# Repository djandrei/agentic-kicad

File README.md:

# Agentic KiCad

This fork of [KiCad](https://kicad.org) lets an AI agent design electronics with KiCad's own
engine. An MCP server runs inside KiCad, and every program is available to the agent as
structured tools (148 of them): schematics and hierarchy, symbol and footprint libraries,
boards with interactive routing, length tuning and zones, ERC and DRC, SPICE simulation, 3D,
Gerbers, drawing sheets, the calculator and footprint assignment. Any MCP client works,
for example Claude Code:

```bash
claude mcp add kicad -- /path/to/kicad-cli mcp --stdio      # headless
kicad --mcp-port 0                                          # with viewers; prints the URL and token
```

Every change is saved at once and is one step of the project's file history, so `undo`
and `redo` work across all programs. In viewer mode a person watches read-only viewers that
follow the agent (they never change the design) and can pause it. `kicad --classic` starts
KiCad's usual GUI. Fork code lives in `agentic/`; upstream files are touched only by small,
documented hooks, and the fork is off unless built with `-DKICAD_AGENTIC=ON`.

Documentation: [overview](doc/agentic/README.md), [connecting a client](doc/agentic/clients.md),
[tool reference](doc/agentic/tools.md), [upstream merges](doc/agentic/upstream-merge.md).

### The viewers

The pictures below come from one session in which an agent designed a 4-layer sensor board
and simulated its amplifier stage.

| | |
|---|---|
|  |  |
| **Hub**: open projects, their files, every call the agent makes, a button per viewer and Pause. | **Schematic**: follows the sheet the agent edits and highlights the change; hierarchy, ERC and nets beside it. |
|  |  |
| **PCB**: the board as the agent routes it, with layers, unrouted connections and DRC results. | **3D**: reloads after each board change and uses the camera the agent sets. |
|  |  |
| **Symbol editor**: the symbol the agent builds or inspects, unit by unit, with its pins. | **Footprint editor**: the footprint being built, with its pads. |
|  | |
| **Simulator**: the signals and measurements of the last ngspice run, with the netlist. | |

---

# KiCad README

For specific documentation about [building KiCad](https://dev-docs.kicad.org/en/build/), policies
and guidelines, and source code documentation see the
[Developer Documentation](https://dev-docs.kicad.org) website.

You may also take a look into the [Wiki](https://gitlab.com/kicad/code/kicad/-/wikis/home),
the [contribution guide](https://dev-docs.kicad.org/en/contribute/).

For general information about KiCad and information about contributing to the documentation and
libraries, see our [Website](https://kicad.org/) and our [Forum](https://forum.kicad.info/).

## Build state

KiCad uses a host of CI resources.

GitLab CI pipeline status can be viewed for Linux and Windows builds of the latest commits.

## Release status

## Files
* [AUTHORS.txt](AUTHORS.txt) - The authors, contributors, document writers and translators list
* [CMakeLists.txt](CMakeLists.txt) - Main CMAKE build tool script
* [copyright.h](copyright.h) - A very short copy of the GNU General Public License to be included in new source files
* [Doxyfile](Doxyfile) - Doxygen config file for KiCad
* [INSTALL.txt](INSTALL.txt) - The release (binary) installation instructions
* [uncrustify.cfg](uncrustify.cfg) - Uncrustify config file for uncrustify sources formatting tool
* [_clang-format](_clang-format) - clang config file for clang-format sources formatting tool

## Subdirectories

* [3d-viewer](3d-viewer)         - Sourcecode of the 3D viewer
* [cmake](cmake)      - Modules for the CMAKE build tool
* [common](common)            - Sourcecode of the common library
* [cvpcb](cvpcb)             - Sourcecode of the CvPCB tool
* [demos](demos)             - Some demo examples
* [doxygen](doxygen)     - Configuration for generating pretty doxygen manual of the codebase
* [eeschema](eeschema)          - Sourcecode of the schematic editor
* [gerbview](gerbview)          - Sourcecode of the gerber viewer
* [include](include)           - Interfaces to the common library
* [kicad](kicad)             - Sourcecode of the project manager
* [libs](libs)           - Sourcecode of KiCad utilities (geometry and others)
* [pagelayout_editor](pagelayout_editor) - Sourcecode of the pagelayout editor
* [patches](patches)           - Collection of patches for external dependencies
* [pcbnew](pcbnew)           - Sourcecode of the printed circuit board editor
* [plugins](plugins)           - Sourcecode for the 3D viewer plugins
* [qa](qa)                - Unit testing framework for KiCad
* [resources](resources)         - Packaging resources such as bitmaps and operating system specific files
    - [bitmaps_png](resources/bitmaps_png)       - Menu and program icons
    - [project_template](resources/project_template)          - Project template
* [thirdparty](thirdparty)           - Sourcecode of external libraries used in KiCad but not written by the KiCad team
* [tools](tools)             - Helpers for developing, testing and building
* [translation](translation) - Translation data files (managed through [Weblate](https://hosted.weblate.org/projects/kicad/master-source/) for most languages)
* [utils](utils)             - Small utils for KiCad, e.g. IDF, STEP, and OGL tools and converters

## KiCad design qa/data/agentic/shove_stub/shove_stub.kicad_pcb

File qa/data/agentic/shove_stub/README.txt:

The eco_logger board of the third scripted tool test, before U2.6 -> J2.2 was routed. That route
needs shove mode, and the shove broke the +5V track next to J2.2 into two pieces that led nowhere
(the net stayed connected another way); pcb_route now removes such copper (test_tool_findings.py).

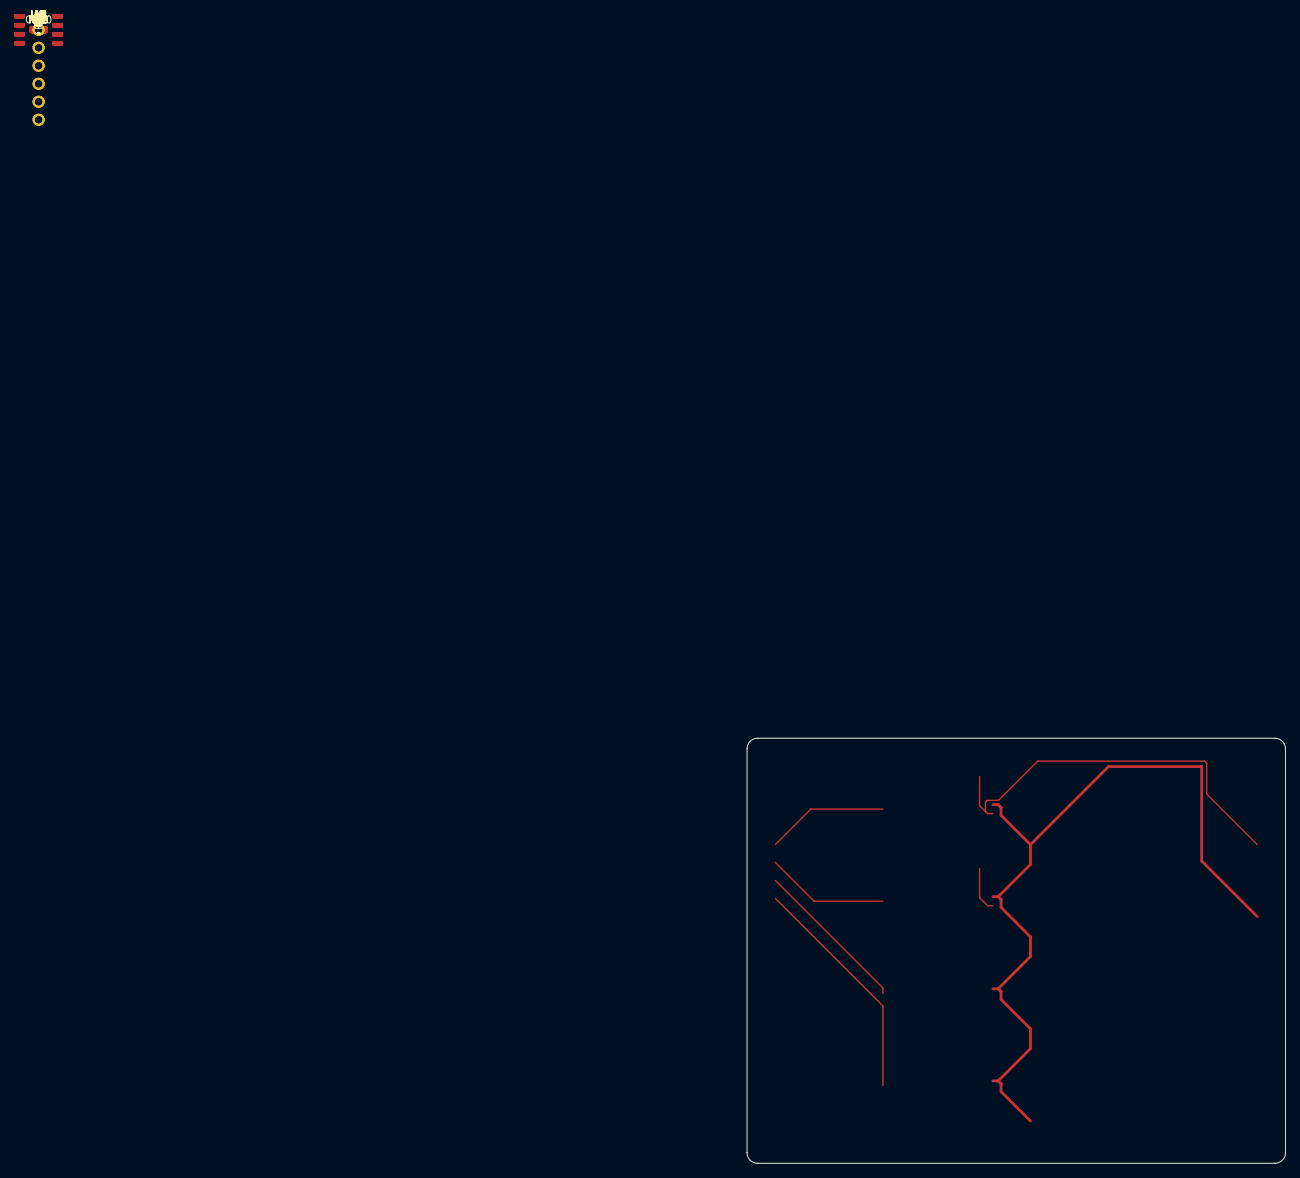
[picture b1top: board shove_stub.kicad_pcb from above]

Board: 2 copper layers, 76.0 x 60.0 mm, 23 parts (0 on the bottom side), 14 nets.

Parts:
C1, C2, C3, C4: 100n; R_0603_1608Metric
C100: 10u; R_0603_1608Metric
J1: INPUTS; HDR6
J2: OUTPUTS; HDR6
R1, R4, R7, R10: 100; R_0603_1608Metric
R2, R5, R8, R11: 1k; R_0603_1608Metric
R3, R6, R9, R12: 10k; R_0603_1608Metric
U1, U2, U3, U4: OPA; SOIC-8

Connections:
+5V: C1.1, C2.1, C3.1, C4.1, C100.1, J2.5, U1.7 (V+), U2.7 (V+), U3.7 (V+), U4.7 (V+)
/IN1: J1.1, R1.1
/IN2: J1.2, R4.1
/IN3: J1.3, R7.1
/IN4: J1.4, R10.1
/OUT1: J2.1, R3.2, U1.6
/OUT2: J2.2, R6.2, U2.6
/OUT3: J2.3, R9.2, U3.6
/OUT4: J2.4, R12.2, U4.6
/ch1/N: R1.2, R2.1, R3.1, U1.2 (-), U1.3 (+)
/ch2/N: R4.2, R5.1, R6.1, U2.2 (-), U2.3 (+)
/ch3/N: R7.2, R8.1, R9.1, U3.2 (-), U3.3 (+)
/ch4/N: R10.2, R11.1, R12.1, U4.2 (-), U4.3 (+)
GND: C1.2, C2.2, C3.2, C4.2, C100.2, J1.5, J1.6, J2.6, R2.2, R5.2, R8.2, R11.2, U1.4 (V-), U2.4 (V-), U3.4 (V-), U4.4 (V-)

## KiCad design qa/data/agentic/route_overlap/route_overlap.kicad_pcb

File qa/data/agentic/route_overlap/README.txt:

The psu_monitor board of the second scripted tool test, without the /ALERT tracks and the zones.
Routing J2.3 -> U1.7 and then U1.7 -> R6.1 here made the second route follow the first one's
track out of U1.7, doubling 4.5 mm of copper (test_tool_findings.py).

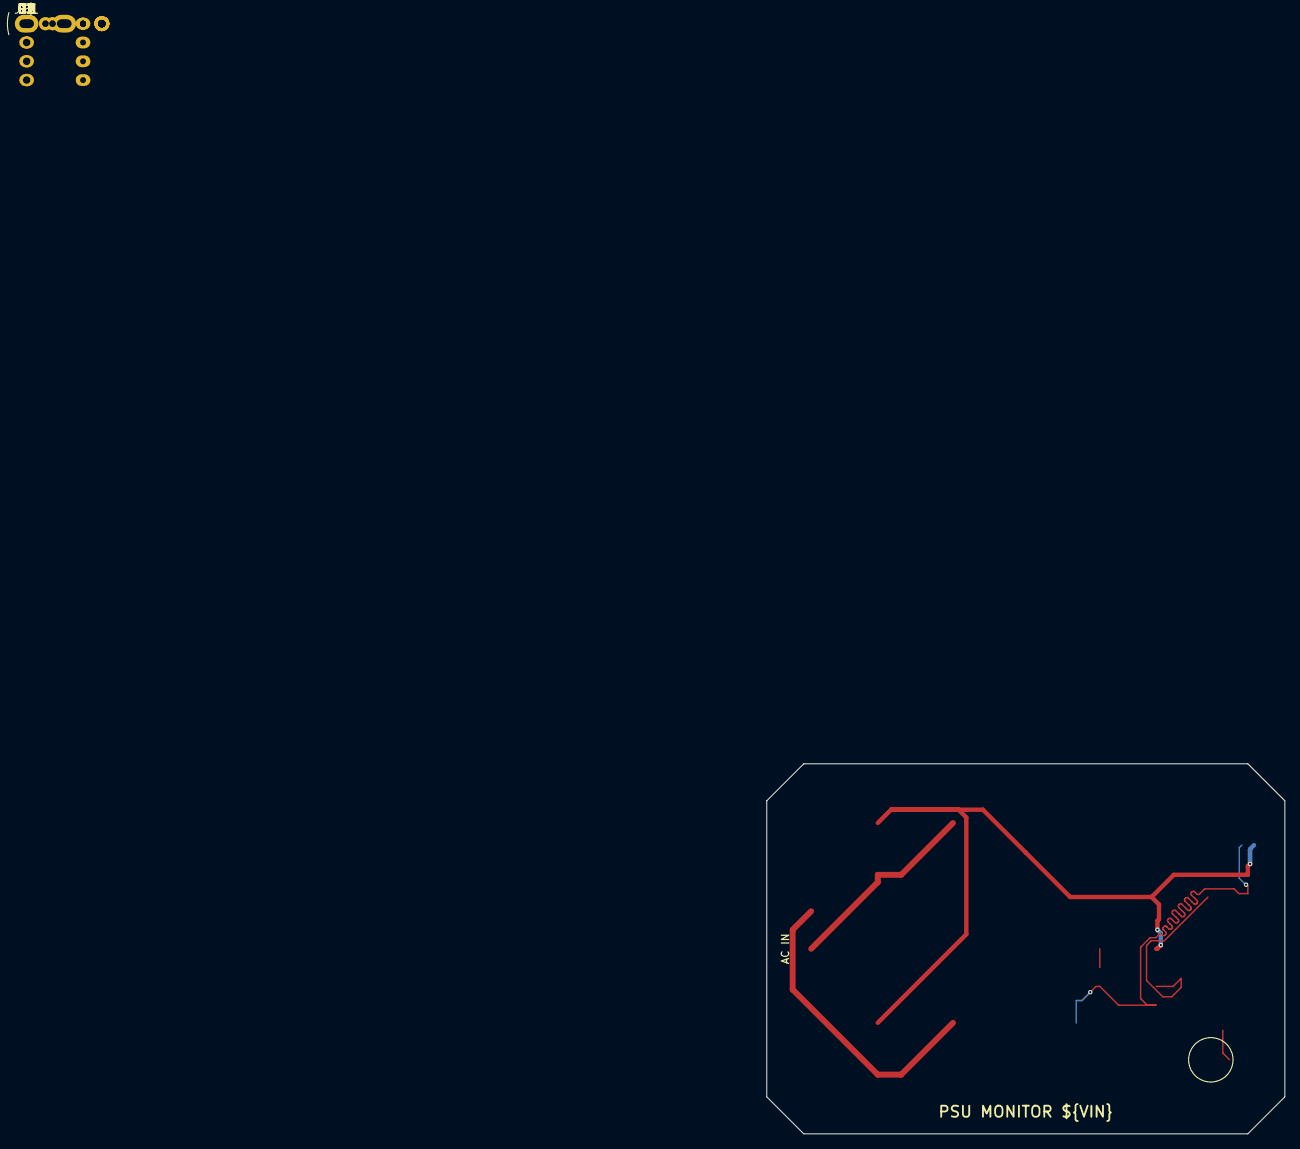
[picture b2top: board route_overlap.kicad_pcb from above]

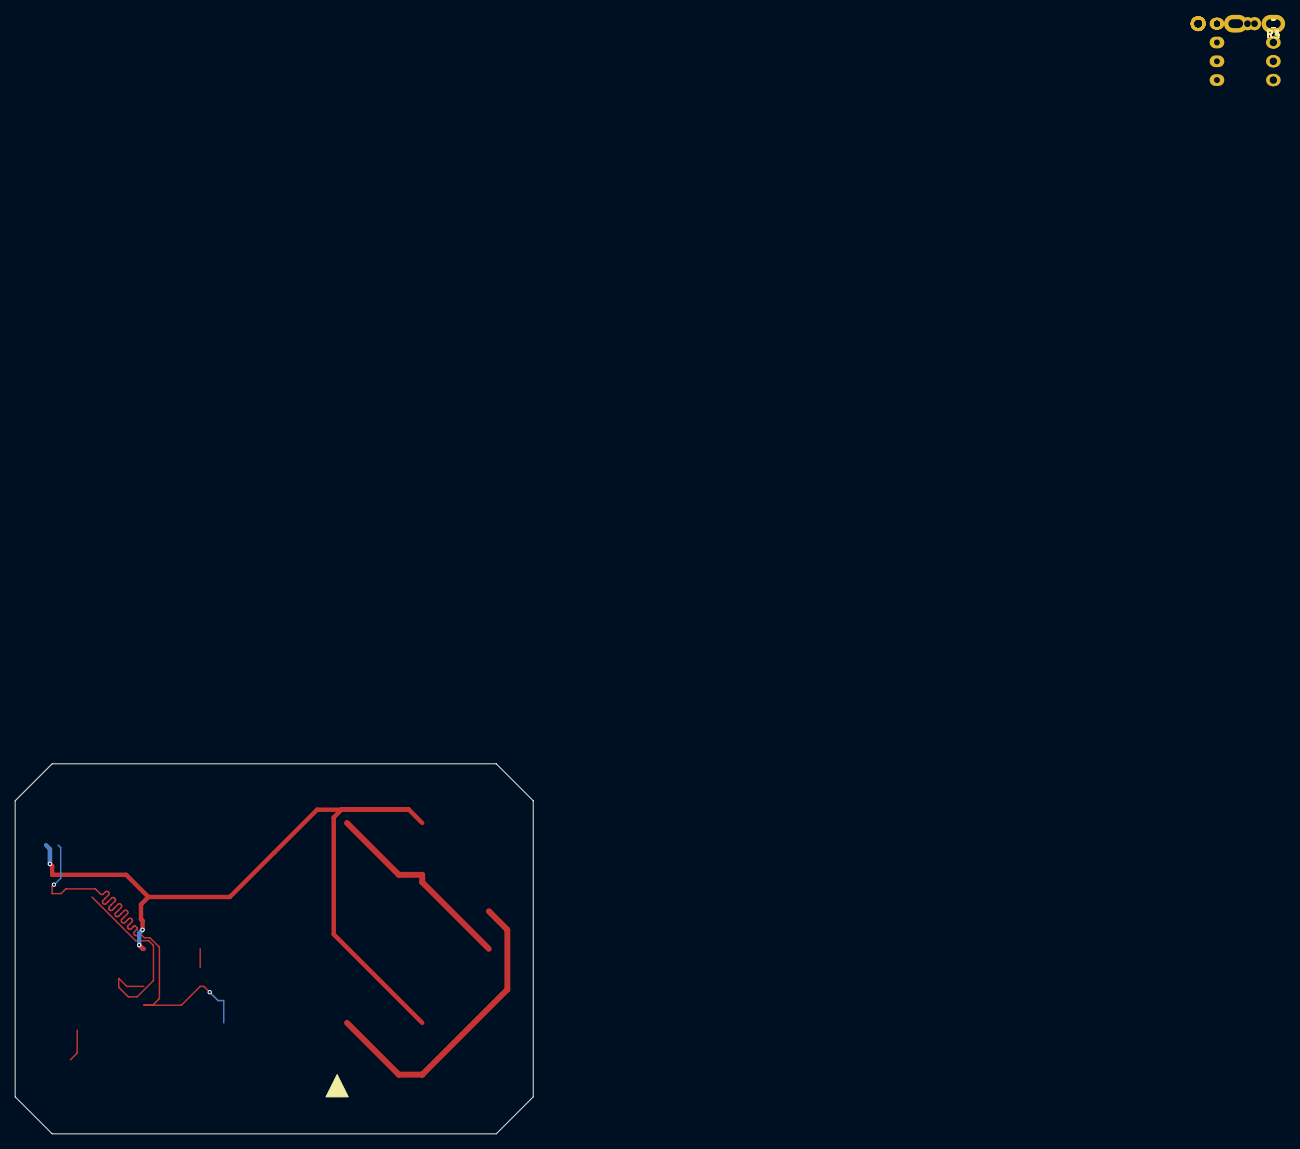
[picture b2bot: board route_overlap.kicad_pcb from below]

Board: 2 copper layers, 70.0 x 50.0 mm, 17 parts (3 on the bottom side), 9 nets.

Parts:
C1: 470u; CP_D8
D1, D2, D3, D4: 1N4007; DO-41
D5: red; LED_3MM
D6: 5V1; DO-41
J1: AC_IN; TERM2_5.08
J2: OUT; HDR4
JP1: JP_TRAP
R1: 100k; R_0603_1608Metric
R2, R6: 1k; R_AXIAL
R3, R4: 10k; R_0603_1608Metric
R5: 10k; R_AXIAL
U1: OPA2; DIP-8

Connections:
/AC1: D1.2 (A), D2.1 (K), J1.1
/AC2: D3.2 (A), D4.1 (K), J1.2
/ALERT: J2.3 (ALERT), R6.1, U1.7
/VSENSE: J2.2 (SENSE), R1.2, R3.1, R4.1, U1.3 (+), U1.5 (+)
/monitor/REF: D6.1 (K), R5.2, U1.6 (-)
GND: C1.2, D2.2 (A), D4.2 (A), D5.1 (K), D6.2 (A), J2.4 (GND), R2.2, R3.2, R4.2, U1.4 (V-)
unnamed: D5.2 (A), R6.2
SENSE_BUF: U1.1, U1.2 (-)
VRAW: C1.1, D1.1 (K), D3.1 (K), J2.1 (VRAW), R1.1, R2.1, R5.1, U1.8 (V+)
